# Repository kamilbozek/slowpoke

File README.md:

# Slowpoke (ヤドン)
Slowpoke (ヤドン) is a 34-key split keyboard.

Features:
* choc spacing
* Pro Micro compatible
* supports Kailh hotswap sockets
* reversible PCB

## Thanks
* [@tapioki](https://github.com/tapioki) for [Architeuthis dux](https://github.com/tapioki/cephalopoda/tree/main/Architeuthis%20dux) which heavily inspired this keyboard
* FlatFootFox for [a great series of articles about designing a keyboard with Ergogen and KiCad](https://flatfootfox.com/ergogen-introduction/)

## Changelog
### 0.1.0
The initial version of the keyboard.

This version has a routing bug that requires switching pins `P02` and `P21` so that the TRRS socket is routed to the `P02` and the inner column is routed to `P21`.

See [how to fix routing](docs/routing-fix.md).

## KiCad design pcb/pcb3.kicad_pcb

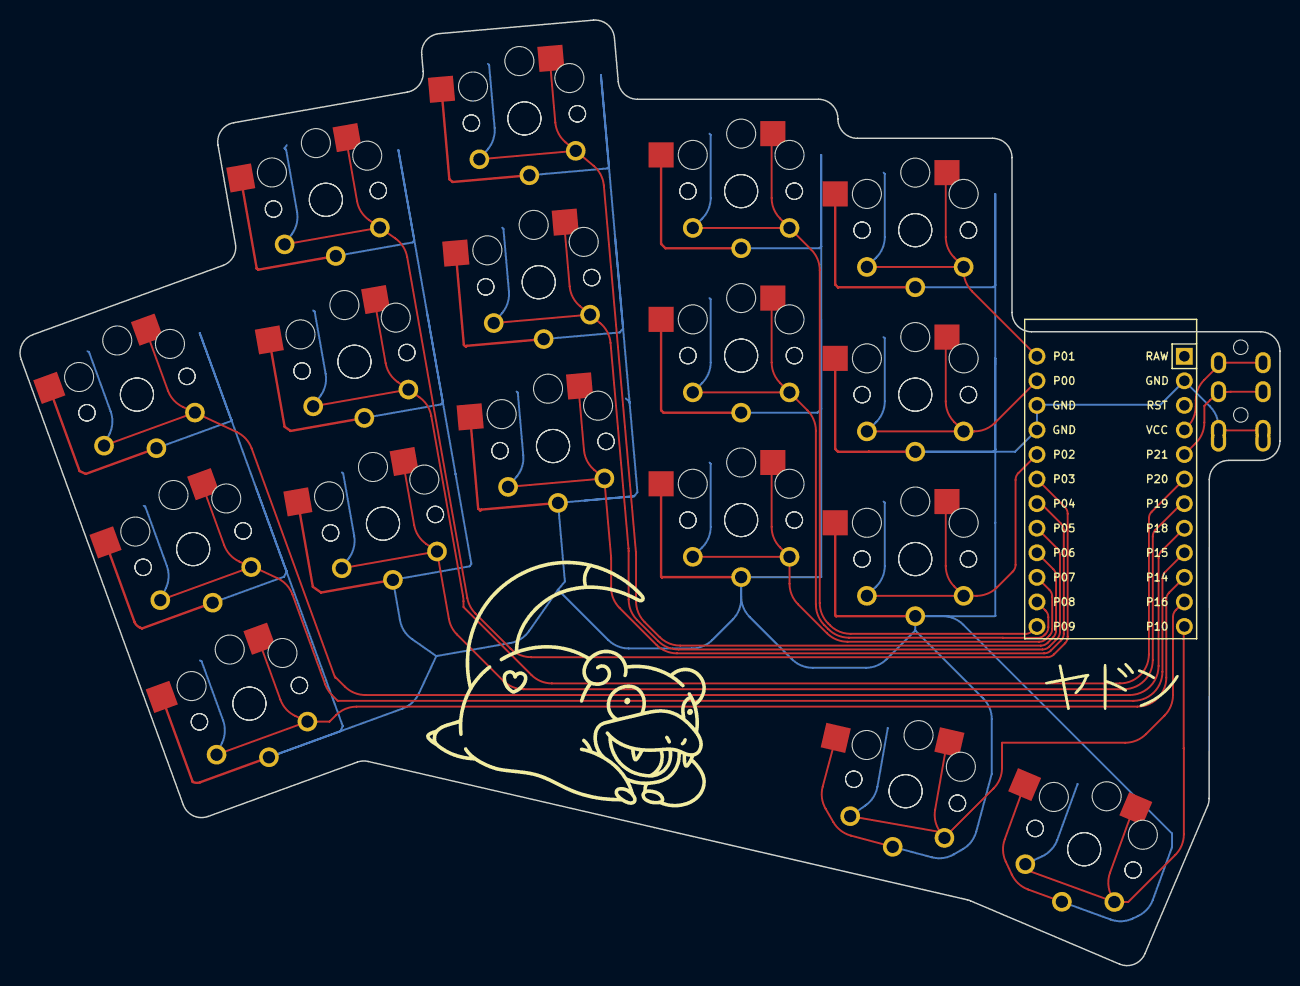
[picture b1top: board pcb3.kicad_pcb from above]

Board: 2 copper layers, 130.2 x 97.8 mm, 36 parts (0 on the bottom side), 20 nets.

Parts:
MCU1: ProMicro
S1, S2, S3, S4, S5, S6, S7, S8, S9, S10, S11, S12, S13, S14, S15, S16, S17, S18, S19, S20, S21, S22, S23, S24, S25, S26, S27, S28, S29, S30, S31, S32, S33, S34: PG1350
TRRS1: TRRS-PJ-320A-dual

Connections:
GND: MCU1.2, MCU1.15, MCU1.16, S1.2, S2.2, S3.2, S4.2, S5.2, S6.2, S7.2, S8.2, S9.2, S10.2, S11.2, S12.2, S13.2, S14.2, S15.2, S16.2, S17.2, S18.2, S19.2, S20.2, S21.2, S22.2, S23.2, S24.2, S25.2, S26.2, S27.2, S28.2, S29.2, S30.2, S31.2, S32.2, S33.2, S34.2, TRRS1.1, TRRS1.2
P0: MCU1.14, S14.1, S31.1
P1: MCU1.13, S15.1, S32.1
P2: MCU1.17, S13.1, S30.1
P3: MCU1.18, S6.1, S23.1
P4: MCU1.19, S7.1, S24.1
P5: MCU1.20, S8.1, S25.1
P6: MCU1.21, S9.1, S26.1
P7: MCU1.22, S10.1, S27.1
P8: MCU1.23, S11.1, S28.1
P9: MCU1.24, S12.1, S29.1
P10: MCU1.12, S17.1, S34.1
P14: MCU1.10, S1.1, S18.1
P15: MCU1.9, S2.1, S19.1
P16: MCU1.11, S16.1, S33.1
P18: MCU1.8, S3.1, S20.1
P19: MCU1.7, S4.1, S21.1
P20: MCU1.6, S5.1, S22.1
P21: MCU1.5, TRRS1.3
VCC: MCU1.4, TRRS1.4

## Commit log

2024-01-11 slowpoke 0.1.0
2024-02-09 Updated pictures
2024-02-09 Added todos
